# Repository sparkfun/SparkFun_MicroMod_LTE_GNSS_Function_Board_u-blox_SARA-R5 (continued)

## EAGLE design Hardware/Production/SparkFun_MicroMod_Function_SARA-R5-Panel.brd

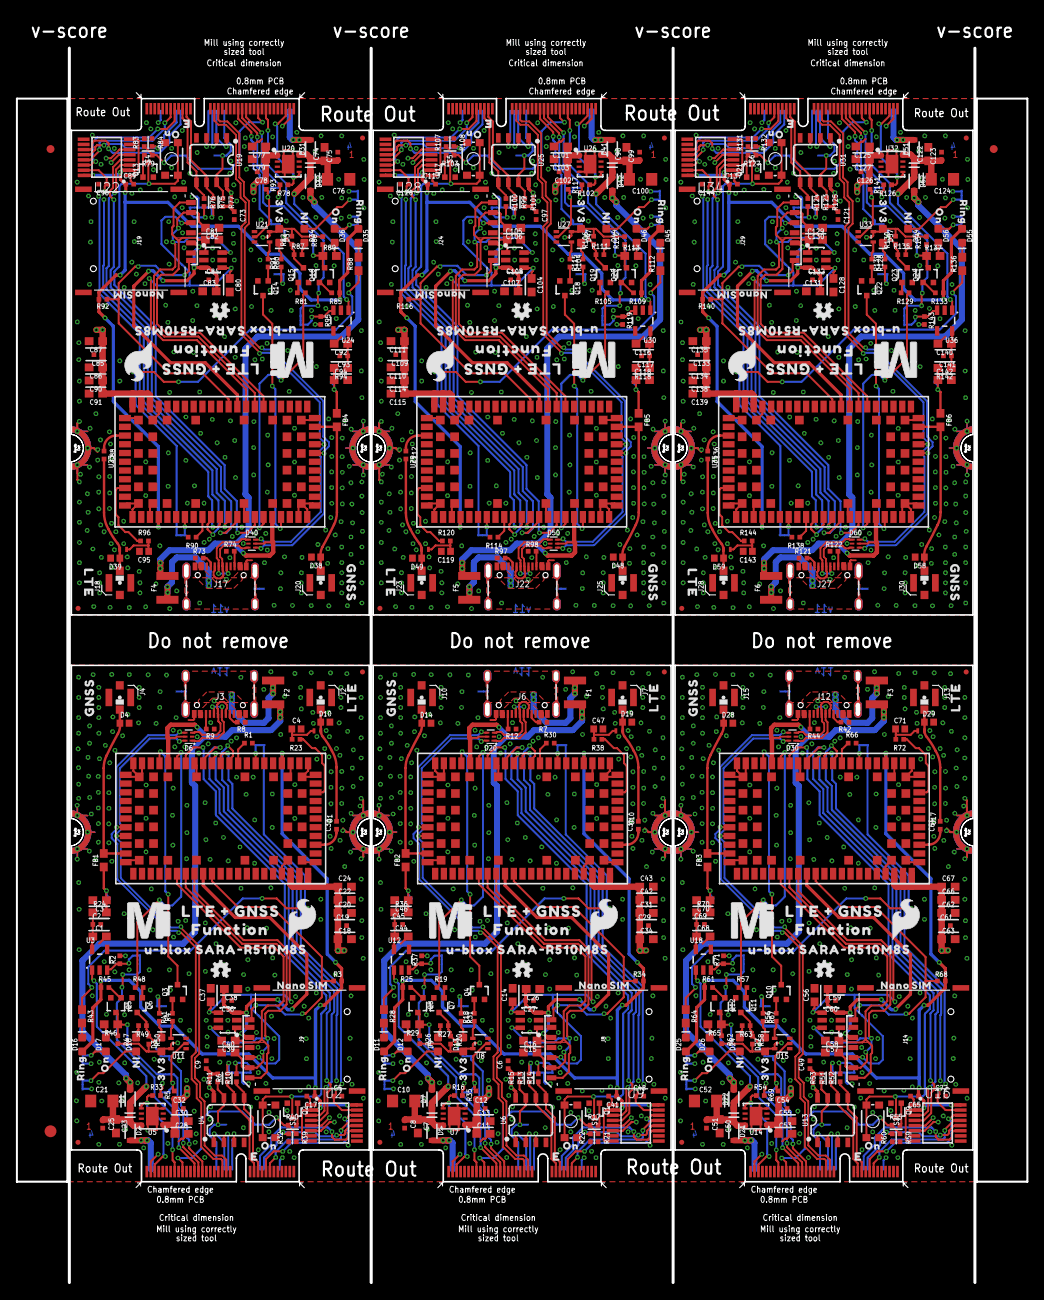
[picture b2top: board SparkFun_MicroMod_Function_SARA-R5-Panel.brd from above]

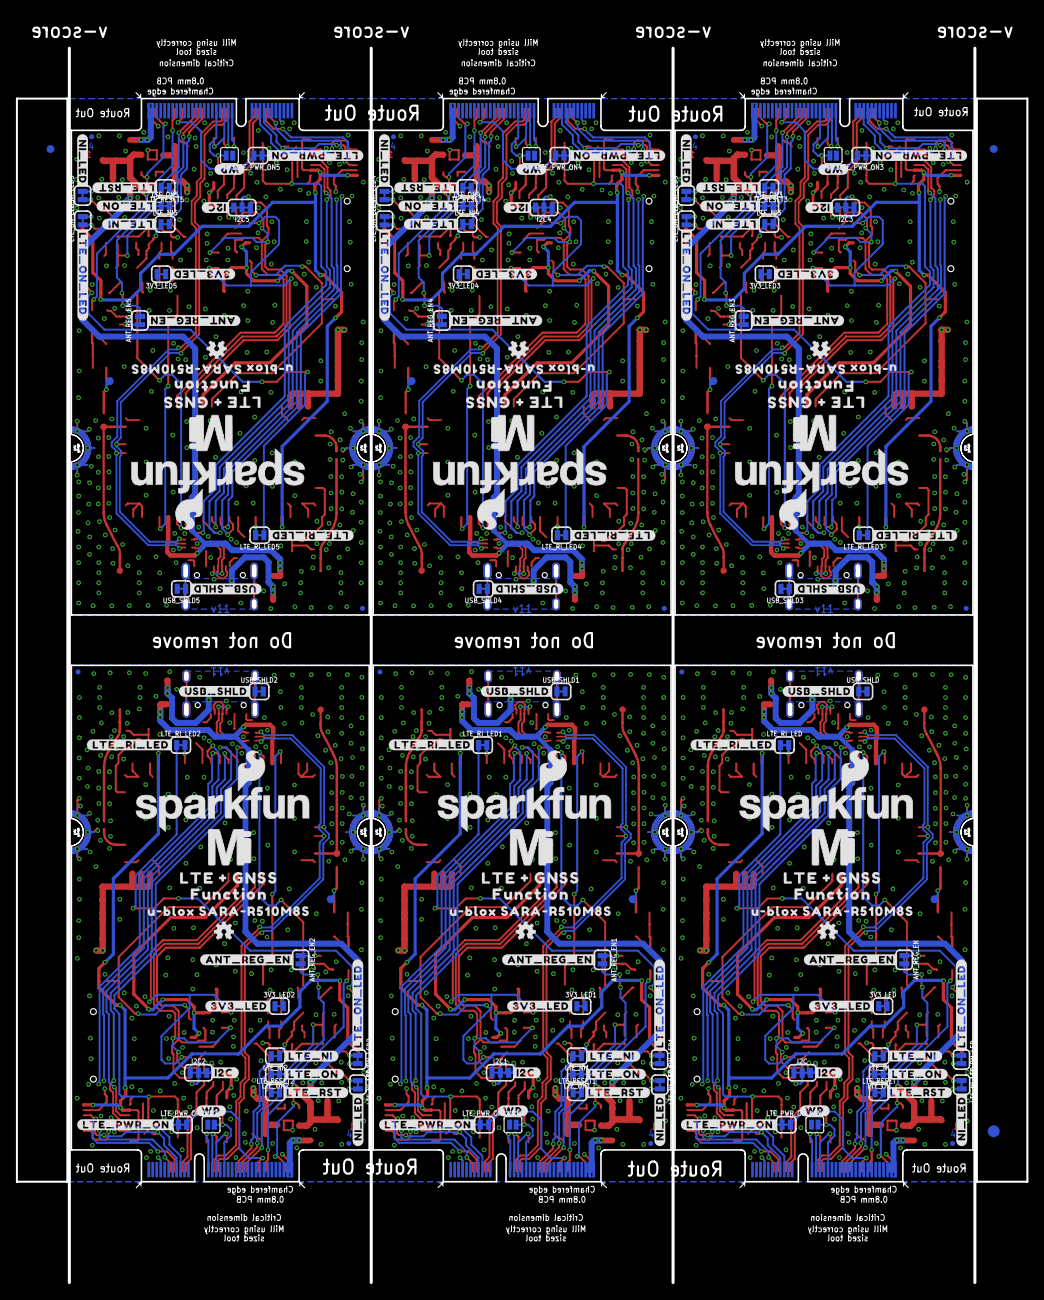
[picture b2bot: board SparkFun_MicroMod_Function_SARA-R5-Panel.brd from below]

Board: 4 copper layers, 127.2 x 155.4 mm, 768 parts (201 on the bottom side), 432 nets.

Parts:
3V3_LED, 3V3_LED1, 3V3_LED2, 3V3_LED3, 3V3_LED4, 3V3_LED5: JUMPER-SMT_2_NC_TRACE_SILK; SMT-JUMPER_2_NC_TRACE_SILK
ANT_REG_EN, ANT_REG_EN1, ANT_REG_EN2, ANT_REG_EN3, ANT_REG_EN4, ANT_REG_EN5: JUMPER-SMT_2_NC_TRACE_SILK; SMT-JUMPER_2_NC_TRACE_SILK
C1, C44, C68, C92, C116, C140: 1.0uF; 0603
C2, C5, C6, C8, C9, C12, C17, C19, C25, C27, C29, C32, C36, C41, C45, C48, C49, C51, C54, C60, C61, C65, C69, C72, C73, C75, C78, C84, C85, C89, C93, C96, C97, C99, C102, C108, C109, C113, C117, C120, C121, C123, C126, C132, C133, C137, C141, C144: 0.1uF; 0402-TIGHT
C3, C14, C15, C16, C26, C37, C38, C39, C40, C46, C56, C57, C58, C59, C70, C80, C81, C82, C83, C94, C104, C105, C106, C107, C118, C128, C129, C130, C131, C142: 47pF; 0603
C4, C47, C71, C95, C119, C143: 27pF; 0402
C7, C13, C23, C30, C50, C55, C74, C79, C98, C103, C122, C127: 0.22uF; 0603
C10, C21, C52, C76, C100, C124: 10uF; EIA3216
C11, C28, C53, C77, C101, C125: 4.7uF; 0603
C18, C34, C63, C87, C111, C135: 10uF; 0603
C20, C31, C62, C86, C110, C134: 68pF; 0603
C22, C42, C66, C90, C114, C138: 15pF; 0603
C24, C43, C67, C91, C115, C139: 8.2pF; 0603
C33, C35, C64, C88, C112, C136: 33pF; 0402-TIGHT
D1, D2, D5, D7, D21, D22, D31, D32, D41, D42, D51, D52: 3A/10V/280mV; SOD-323
D3, D11, D12, D13, D16, D17, D25, D26, D27, D35, D36, D37, D45, D46, D47, D55, D56, D57: RED; LED-0603
D4, D10, D14, D19, D28, D29, D38, D39, D48, D49, D58, D59: PESD0402-0402; 0402
D6, D20, D30, D40, D50, D60: PRTR5V0U2F; SOT886
D8, D15, D23, D33, D43, D53: DT1042-04SO-7; SOT23-6L
D9, D18, D24, D34, D44, D54: BLUE; LED-0603
E$1, E$2, E$3, E$4: FIDUCIAL-1X2
E$5, E$6: FIDUCIAL-1.5X3
F1, F2, F3, F4, F5, F6: 6V/2A; 1210
FB1, FB2, FB3, FB4, FB5, FB6: 30Ω/1.8A; 0603
FD1, FD2, FD3, FD4, FD5, FD6, FD7, FD8, FD9, FD10, FD11, FD12, FD13, FD14, FD15, FD16, FD17, FD18, FD19, FD20, FD21, FD22, FD23, FD24: FIDUCIALUFIDUCIAL; FIDUCIAL-MICRO
I2C, I2C1, I2C2, I2C3, I2C4, I2C5: JUMPER-SMT_3_2-NC_TRACE_SILK; SMT-JUMPER_3_2-NC_TRACE_SILK
J1, J5, J11, J16, J21, J26: MICROMOD_FUNCTION_STANDARD; M.2-CARD-E-22_FUNCTION_STANDARD
J2, J4, J7, J10, J13, J15, J18, J20, J23, J25, J28, J30: U.FL
J3, J6, J12, J17, J22, J27: USB-C-16P-2LAYER-PADS
J8, J9, J14, J19, J24, J29: NANO_SIM; NANO_SIM_PP
L1, L2, L3, L4, L5, L6: 68nH; 0402_COILCRAFT
LOGO1, LOGO3, LOGO9, LOGO13, LOGO17, LOGO21: SFE_LOGO_NAME_FLAME.2_INCH; SFE_LOGO_NAME_FLAME_.2
LOGO2, LOGO5, LOGO10, LOGO14, LOGO18, LOGO22: SFE_LOGO_FLAME.2_INCH; SFE_LOGO_FLAME_.2
LOGO4, LOGO6, LOGO7, LOGO8, LOGO11, LOGO12, LOGO15, LOGO16, LOGO19, LOGO20, LOGO23, LOGO24: OSHW-LOGOMINI; OSHW-LOGO-MINI
LTE_NI, LTE_NI1, LTE_NI2, LTE_NI3, LTE_NI4, LTE_NI5: JUMPER-SMT_2_NC_TRACE_SILK; SMT-JUMPER_2_NC_TRACE_SILK
LTE_NI_LED, LTE_NI_LED1, LTE_NI_LED2, LTE_NI_LED3, LTE_NI_LED4, LTE_NI_LED5: JUMPER-SMT_2_NC_TRACE_SILK; SMT-JUMPER_2_NC_TRACE_SILK
LTE_ON, LTE_ON1, LTE_ON2, LTE_ON3, LTE_ON4, LTE_ON5: JUMPER-SMT_2_NC_TRACE_SILK; SMT-JUMPER_2_NC_TRACE_SILK
LTE_ON_LED, LTE_ON_LED1, LTE_ON_LED2, LTE_ON_LED3, LTE_ON_LED4, LTE_ON_LED5: JUMPER-SMT_2_NC_TRACE_SILK; SMT-JUMPER_2_NC_TRACE_SILK
LTE_PWR_ON, LTE_PWR_ON1, LTE_PWR_ON2, LTE_PWR_ON3, LTE_PWR_ON4, LTE_PWR_ON5: JUMPER-SMT_2_NC_TRACE_SILK; SMT-JUMPER_2_NC_TRACE_SILK
LTE_RESET, LTE_RESET1, LTE_RESET2, LTE_RESET3, LTE_RESET4, LTE_RESET5: JUMPER-SMT_2_NC_TRACE_SILK; SMT-JUMPER_2_NC_TRACE_SILK
LTE_RI_LED, LTE_RI_LED1, LTE_RI_LED2, LTE_RI_LED3, LTE_RI_LED4, LTE_RI_LED5: JUMPER-SMT_2_NC_TRACE_SILK; SMT-JUMPER_2_NC_TRACE_SILK
Q1, Q2, Q3, Q4, Q5, Q6, Q7, Q8, Q9, Q10, Q11, Q12, Q13, Q14, Q15, Q16, Q17, Q18, Q19, Q20, Q21, Q22, Q23, Q24: 310mA/60V/1.6Ω; SOT323
R1, R2, R3, R20, R21, R22, R26, R30, R32, R34, R37, R39, R47, R50, R58, R59, R60, R62, R66, R68, R71, R82, R83, R84, R86, R90, R92, R95, R106, R107, R108, R110, R114, R116, R119, R130, R131, R132, R134, R138, R140, R143: 100k; 0402-TIGHT
R4, R31, R67, R91, R115, R139: 4.7k; 0402-TIGHT
R5, R11, R15, R23, R35, R38, R53, R69, R72, R77, R93, R96, R101, R117, R120, R125, R141, R144: 10k; 0402-TIGHT
R6, R10, R13, R14, R27, R49, R51, R52, R63, R75, R76, R87, R99, R100, R111, R123, R124, R135: 2.2k; 0402-TIGHT
R7, R8, R9, R12, R42, R44, R73, R74, R97, R98, R121, R122: 5.1k; 0402-TIGHT
R16, R33, R54, R78, R102, R126: DNP; 0402-TIGHT
R17, R18, R19, R25, R40, R41, R45, R48, R55, R56, R57, R61, R79, R80, R81, R85, R103, R104, R105, R109, R127, R128, R129, R133: 1k; 0402-TIGHT
R24, R36, R70, R94, R118, R142: 10; 0603
R28, R43, R64, R88, R112, R136: 240; 0603
R29, R46, R65, R89, R113, R137: 100; 0603
S1, S2, S3, S4, S5, S6: PWR_ON; TACTILE_SWITCH_SMD_4.6X2.8MM
TP1, TP2, TP3, TP4, TP5, TP22: TEST-POINT3X4; PAD.03X.04
U1, U10, U17, U23, U29, U35: SARA-R510M8S; SARA-LGA
U2, U9, U16, U22, U28, U34: SN74AVC4T774PW; SOP65P640X120-16N
U3, U12, U18, U24, U30, U36: 3.3V; SOT23-5
U4, U6, U13, U19, U25, U31: EEPROM; SO08
U5, U7, U14, U20, U26, U32: AP7361C-33FGE; UDFN-8
U8, U11, U15, U21, U27, U33: 74HC1G04; SOT353
U$1, U$50, U$81, U$110, U$140, U$169: #I2C#0
U$2, U$48, U$78, U$108, U$138, U$167: #ANT_REG_EN#0
U$3, U$12, U$35, U$36, U$65, U$66, U$95, U$96, U$124, U$125, U$154, U$155: MICROMOD_MI_LOGO_1
U$4, U$49, U$79, U$109, U$139, U$168: #3V3_LED#0
U$5, U$27, U$31, U$34, U$59, U$64, U$89, U$94, U$118, U$123, U$148, U$153: ON0
U$6, U$38, U$68, U$98, U$128, U$157: #LTE_ON#2
U$7, U$39, U$69, U$99, U$129, U$158: #LTE_NI#2
U$8, U$37, U$67, U$97, U$127, U$156: #LTE_PWR_ON#1
U$9, U$54, U$85, U$114, U$144, U$173: #NI_LED#0
U$10, U$25, U$56, U$87, U$116, U$146: #WP#0
U$11, U$14, U$40, U$45, U$70, U$75, U$100, U$105, U$130, U$135, U$159, U$164: LTE_#_GNSS0
U$13, U$19, U$41, U$46, U$71, U$76, U$101, U$106, U$131, U$136, U$160, U$165: FUNCTION0
U$15, U$20, U$42, U$47, U$72, U$77, U$102, U$107, U$132, U$137, U$161, U$166: U#BLOX_SARA#R510M8S0
U$16, U$43, U$73, U$103, U$133, U$162: LTE0
U$17, U$44, U$74, U$104, U$134, U$163: GNSS0
U$18, U$32, U$62, U$92, U$121, U$151: NANO0
U$21, U$51, U$82, U$111, U$141, U$170: #USB_SHLD#0
U$22, U$52, U$83, U$112, U$142, U$171: #LTE_RI_LED#0
U$23, U$53, U$84, U$113, U$143, U$172: #LTE_RST#0
U$24, U$55, U$86, U$115, U$145, U$174: #LTE_ON_LED#0
U$26, U$29, U$58, U$88, U$117, U$147: NI0
U$28, U$57, U$60, U$90, U$119, U$149: 3V34
U$30, U$61, U$80, U$91, U$120, U$150: RING0
U$33, U$63, U$93, U$122, U$126, U$152: SIM0
USB_SHLD, USB_SHLD1, USB_SHLD2, USB_SHLD3, USB_SHLD4, USB_SHLD5: JUMPER-SMT_2_NC_TRACE_SILK; SMT-JUMPER_2_NC_TRACE_SILK
WP, WP1, WP2, WP3, WP4, WP5: SMT-JUMPER_2_NO_SILK

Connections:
3.3V: C5.1, C9.1, C18.1, C19.1, C20.1, C22.1, C24.1, C28.1, C30.1, C32.1, D3.A, I2C.2, LTE_NI_LED.2, LTE_ON_LED.2, R5.1, R11.2, R47.2, R50.2, U1.51, U1.52, U1.53, U2.15, U4.8, U5.1, U11.5
3.3V1: C6.1, C11.1, C12.1, C13.1, C29.1, C31.1, C34.1, C42.1, C43.1, C48.1, D13.A, I2C1.2, LTE_NI_LED1.2, LTE_ON_LED1.2, R15.2, R20.2, R26.2, R35.1, U6.8, U7.1, U8.5, U9.15, U10.51, U10.52, U10.53
3.3V2: C49.1, C53.1, C54.1, C55.1, C61.1, C62.1, C63.1, C66.1, C67.1, C72.1, D27.A, I2C2.2, LTE_NI_LED2.2, LTE_ON_LED2.2, R53.2, R58.2, R62.2, R69.1, U13.8, U14.1, U15.5, U16.15, U17.51, U17.52, U17.53
3.3V3: C73.1, C77.1, C78.1, C79.1, C85.1, C86.1, C87.1, C90.1, C91.1, C96.1, D37.A, I2C3.2, LTE_NI_LED3.2, LTE_ON_LED3.2, R77.2, R82.2, R86.2, R93.1, U19.8, U20.1, U21.5, U22.15, U23.51, U23.52, U23.53
3.3V4: C97.1, C101.1, C102.1, C103.1, C109.1, C110.1, C111.1, C114.1, C115.1, C120.1, D47.A, I2C4.2, LTE_NI_LED4.2, LTE_ON_LED4.2, R101.2, R106.2, R110.2, R117.1, U25.8, U26.1, U27.5, U28.15, U29.51, U29.52, U29.53
3.3V5: C121.1, C125.1, C126.1, C127.1, C133.1, C134.1, C135.1, C138.1, C139.1, C144.1, D57.A, I2C5.2, LTE_NI_LED5.2, LTE_ON_LED5.2, R125.2, R130.2, R134.2, R141.1, U31.8, U32.1, U33.5, U34.15, U35.51, U35.52, U35.53
3.3V_IN: J1.73, R2.2, R33.2
3.3V_IN1: J5.73, R16.2, R37.2
3.3V_IN2: J11.73, R54.2, R71.2
3.3V_IN3: J16.73, R78.2, R95.2
3.3V_IN4: J21.73, R102.2, R119.2
3.3V_IN5: J26.73, R126.2, R143.2
ANT_REG_EN: ANT_REG_EN.1, R2.1, U3.3
ANT_REG_EN1: ANT_REG_EN1.1, R37.1, U12.3
ANT_REG_EN2: ANT_REG_EN2.1, R71.1, U18.3
ANT_REG_EN3: ANT_REG_EN3.1, R95.1, U24.3
ANT_REG_EN4: ANT_REG_EN4.1, R119.1, U30.3
ANT_REG_EN5: ANT_REG_EN5.1, R143.1, U36.3
CTS: J1.18, U2.11
CTS1: J5.18, U9.11
CTS2: J11.18, U16.11
CTS3: J16.18, U22.11
CTS4: J21.18, U28.11
CTS5: J26.18, U34.11
EN: J1.71, R33.1, U5.5
EN1: J5.71, R16.1, U7.5
EN2: J11.71, R54.1, U14.5
EN3: J16.71, R78.1, U20.5
EN4: J21.71, R102.1, U26.5
EN5: J26.71, R126.1, U32.5
EWP: J1.40, R11.1, U4.7, WP.2
EWP1: J5.40, R15.1, U6.7, WP1.2
EWP2: J11.40, R53.1, U13.7, WP2.2
EWP3: J16.40, R77.1, U19.7, WP3.2
EWP4: J21.40, R101.1, U25.7, WP4.2
EWP5: J26.40, R125.1, U31.7, WP5.2
GND: 3V3_LED.1, C1.2, C2.2, C3.2, C4.2, C5.2, C9.2, C17.2, C18.2, C19.2, C20.2, C21.-, C22.2, C23.2, C24.2, C25.2, C28.2, C30.2, C32.2, C36.1, C37.2, C38.1, C39.2, C40.1, D4.2, D6.2, D10.2, D15.2, D15.5, J1.1, J1.2, J1.8, J1.33, J1.39, J1.45, J1.75, J1.GND1, J1.GND2, J1.GND3, J1.GND4, J1.GND5, J1.GND6, J2.1, J2.2, J3.GND, J3.GND2, J4.1, J4.2, J9.A1, J9.A2, J9.A3, J9.A4, J9.C5, Q2.2, Q3.2, Q5.2, Q6.2, R1.2, R8.1, R9.1, R32.1, R39.2, S3.3, S3.4, U1.1, U1.3, U1.5, U1.14, U1.20, U1.21, U1.22, U1.30, U1.32, U1.43, U1.50, U1.54, U1.55, U1.57, U1.58, U1.59, U1.60, U1.61, U1.63, U1.64, U1.65, U1.66, U1.67, U1.68, U1.69, U1.70, U1.71, U1.72, U1.73, U1.74, U1.75, U1.76, U1.77, U1.78, U1.79, U1.80, U1.81, U1.82, U1.83, U1.84, U1.85, U1.86, U1.87, U1.88, U1.89, U1.90, U1.91, U1.92, U1.93, U1.94, U1.95, U1.96, U2.1, U2.7, U2.9, U2.10, U3.2, U4.4, U5.4, U5.EP, U11.3, USB_SHLD.2, WP.1
GND1: 3V3_LED1.1, C6.2, C7.2, C8.2, C10.-, C11.2, C12.2, C13.2, C14.2, C15.2, C16.1, C26.1, C27.1, C29.2, C31.2, C34.2, C41.2, C42.2, C43.2, C44.2, C45.2, C46.2, C47.2, C48.2, D8.2, D8.5, D14.2, D19.2, D20.2, J5.1, J5.2, J5.8, J5.33, J5.39, J5.45, J5.75, J5.GND1, J5.GND2, J5.GND3, J5.GND4, J5.GND5, J5.GND6, J6.GND, J6.GND2, J7.1, J7.2, J8.A1, J8.A2, J8.A3, J8.A4, J8.C5, J10.1, J10.2, Q1.2, Q4.2, Q7.2, Q8.2, R7.1, R12.1, R21.2, R22.1, R30.2, S1.3, S1.4, U6.4, U7.4, U7.EP, U8.3, U9.1, U9.7, U9.9, U9.10, U10.1, U10.3, U10.5, U10.14, U10.20, U10.21, U10.22, U10.30, U10.32, U10.43, U10.50, U10.54, U10.55, U10.57, U10.58, U10.59, U10.60, U10.61, U10.63, U10.64, U10.65, U10.66, U10.67, U10.68, U10.69, U10.70, U10.71, U10.72, U10.73, U10.74, U10.75, U10.76, U10.77, U10.78, U10.79, U10.80, U10.81, U10.82, U10.83, U10.84, U10.85, U10.86, U10.87, U10.88, U10.89, U10.90, U10.91, U10.92, U10.93, U10.94, U10.95, U10.96, U12.2, USB_SHLD1.2, WP1.1
GND2: 3V3_LED2.1, C49.2, C50.2, C51.2, C52.-, C53.2, C54.2, C55.2, C56.2, C57.2, C58.1, C59.1, C60.1, C61.2, C62.2, C63.2, C65.2, C66.2, C67.2, C68.2, C69.2, C70.2, C71.2, C72.2, D23.2, D23.5, D28.2, D29.2, D30.2, J11.1, J11.2, J11.8, J11.33, J11.39, J11.45, J11.75, J11.GND1, J11.GND2, J11.GND3, J11.GND4, J11.GND5, J11.GND6, J12.GND, J12.GND2, J13.1, J13.2, J14.A1, J14.A2, J14.A3, J14.A4, J14.C5, J15.1, J15.2, Q9.2, Q10.2, Q11.2, Q12.2, R42.1, R44.1, R59.2, R60.1, R66.2, S2.3, S2.4, U13.4, U14.4, U14.EP, U15.3, U16.1, U16.7, U16.9, U16.10, U17.1, U17.3, U17.5, U17.14, U17.20, U17.21, U17.22, U17.30, U17.32, U17.43, U17.50, U17.54, U17.55, U17.57, U17.58, U17.59, U17.60, U17.61, U17.63, U17.64, U17.65, U17.66, U17.67, U17.68, U17.69, U17.70, U17.71, U17.72, U17.73, U17.74, U17.75, U17.76, U17.77, U17.78, U17.79, U17.80, U17.81, U17.82, U17.83, U17.84, U17.85, U17.86, U17.87, U17.88, U17.89, U17.90, U17.91, U17.92, U17.93, U17.94, U17.95, U17.96, U18.2, USB_SHLD2.2, WP2.1
GND3: 3V3_LED3.1, C73.2, C74.2, C75.2, C76.-, C77.2, C78.2, C79.2, C80.2, C81.2, C82.1, C83.1, C84.1, C85.2, C86.2, C87.2, C89.2, C90.2, C91.2, C92.2, C93.2, C94.2, C95.2, C96.2, D33.2, D33.5, D38.2, D39.2, D40.2, J16.1, J16.2, J16.8, J16.33, J16.39, J16.45, J16.75, J16.GND1, J16.GND2, J16.GND3, J16.GND4, J16.GND5, J16.GND6, J17.GND, J17.GND2, J18.1, J18.2, J19.A1, J19.A2, J19.A3, J19.A4, J19.C5, J20.1, J20.2, Q13.2, Q14.2, Q15.2, Q16.2, R73.1, R74.1, R83.2, R84.1, R90.2, S4.3, S4.4, U19.4, U20.4, U20.EP, U21.3, U22.1, U22.7, U22.9, U22.10, U23.1, U23.3, U23.5, U23.14, U23.20, U23.21, U23.22, U23.30, U23.32, U23.43, U23.50, U23.54, U23.55, U23.57, U23.58, U23.59, U23.60, U23.61, U23.63, U23.64, U23.65, U23.66, U23.67, U23.68, U23.69, U23.70, U23.71, U23.72, U23.73, U23.74, U23.75, U23.76, U23.77, U23.78, U23.79, U23.80, U23.81, U23.82, U23.83, U23.84, U23.85, U23.86, U23.87, U23.88, U23.89, U23.90, U23.91, U23.92, U23.93, U23.94, U23.95, U23.96, U24.2, USB_SHLD3.2, WP3.1
GND4: 3V3_LED4.1, C97.2, C98.2, C99.2, C100.-, C101.2, C102.2, C103.2, C104.2, C105.2, C106.1, C107.1, C108.1, C109.2, C110.2, C111.2, C113.2, C114.2, C115.2, C116.2, C117.2, C118.2, C119.2, C120.2, D43.2, D43.5, D48.2, D49.2, D50.2, J21.1, J21.2, J21.8, J21.33, J21.39, J21.45, J21.75, J21.GND1, J21.GND2, J21.GND3, J21.GND4, J21.GND5, J21.GND6, J22.GND, J22.GND2, J23.1, J23.2, J24.A1, J24.A2, J24.A3, J24.A4, J24.C5, J25.1, J25.2, Q17.2, Q18.2, Q19.2, Q20.2, R97.1, R98.1, R107.2, R108.1, R114.2, S5.3, S5.4, U25.4, U26.4, U26.EP, U27.3, U28.1, U28.7, U28.9, U28.10, U29.1, U29.3, U29.5, U29.14, U29.20, U29.21, U29.22, U29.30, U29.32, U29.43, U29.50, U29.54, U29.55, U29.57, U29.58, U29.59, U29.60, U29.61, U29.63, U29.64, U29.65, U29.66, U29.67, U29.68, U29.69, U29.70, U29.71, U29.72, U29.73, U29.74, U29.75, U29.76, U29.77, U29.78, U29.79, U29.80, U29.81, U29.82, U29.83, U29.84, U29.85, U29.86, U29.87, U29.88, U29.89, U29.90, U29.91, U29.92, U29.93, U29.94, U29.95, U29.96, U30.2, USB_SHLD4.2, WP4.1
GND5: 3V3_LED5.1, C121.2, C122.2, C123.2, C124.-, C125.2, C126.2, C127.2, C128.2, C129.2, C130.1, C131.1, C132.1, C133.2, C134.2, C135.2, C137.2, C138.2, C139.2, C140.2, C141.2, C142.2, C143.2, C144.2, D53.2, D53.5, D58.2, D59.2, D60.2, J26.1, J26.2, J26.8, J26.33, J26.39, J26.45, J26.75, J26.GND1, J26.GND2, J26.GND3, J26.GND4, J26.GND5, J26.GND6, J27.GND, J27.GND2, J28.1, J28.2, J29.A1, J29.A2, J29.A3, J29.A4, J29.C5, J30.1, J30.2, Q21.2, Q22.2, Q23.2, Q24.2, R121.1, R122.1, R131.2, R132.1, R138.2, S6.3, S6.4, U31.4, U32.4, U32.EP, U33.3, U34.1, U34.7, U34.9, U34.10, U35.1, U35.3, U35.5, U35.14, U35.20, U35.21, U35.22, U35.30, U35.32, U35.43, U35.50, U35.54, U35.55, U35.57, U35.58, U35.59, U35.60, U35.61, U35.63, U35.64, U35.65, U35.66, U35.67, U35.68, U35.69, U35.70, U35.71, U35.72, U35.73, U35.74, U35.75, U35.76, U35.77, U35.78, U35.79, U35.80, U35.81, U35.82, U35.83, U35.84, U35.85, U35.86, U35.87, U35.88, U35.89, U35.90, U35.91, U35.92, U35.93, U35.94, U35.95, U35.96, U36.2, USB_SHLD5.2, WP5.1
GNSS_ANT: D4.1, FB1.2, J4.FEED, U1.31
GNSS_ANT1: D14.1, FB2.2, J10.FEED, U10.31
GNSS_ANT2: D28.1, FB3.2, J15.FEED, U17.31
GNSS_ANT3: D38.1, FB4.2, J20.FEED, U23.31
GNSS_ANT4: D48.1, FB5.2, J25.FEED, U29.31
GNSS_ANT5: D58.1, FB6.2, J30.FEED, U35.31
I2C_SCL: J1.21, R6.1, U4.6
I2C_SCL1: J5.21, R13.1, U6.6
I2C_SCL2: J11.21, R51.1, U13.6
I2C_SCL3: J16.21, R75.1, U19.6
I2C_SCL4: J21.21, R99.1, U25.6
I2C_SCL5: J26.21, R123.1, U31.6
I2C_SDA: J1.19, R10.1, U4.5
I2C_SDA1: J5.19, R14.1, U6.5
I2C_SDA2: J11.19, R52.1, U13.5
I2C_SDA3: J16.19, R76.1, U19.5
I2C_SDA4: J21.19, R100.1, U25.5
I2C_SDA5: J26.19, R124.1, U31.5
LTE_18_!RESET!: Q3.3, U1.18
LTE_18_!RESET!1: Q4.3, U10.18
LTE_18_!RESET!2: Q10.3, U17.18
LTE_18_!RESET!3: Q14.3, U23.18
LTE_18_!RESET!4: Q18.3, U29.18
LTE_18_!RESET!5: Q22.3, U35.18
LTE_18_CTS: U1.11, U2.6
LTE_18_CTS1: U9.6, U10.11
LTE_18_CTS2: U16.6, U17.11
LTE_18_CTS3: U22.6, U23.11
LTE_18_CTS4: U28.6, U29.11
LTE_18_CTS5: U34.6, U35.11
LTE_18_DTR: R1.1, U1.9
LTE_18_DTR1: R30.1, U10.9
LTE_18_DTR2: R66.1, U17.9
LTE_18_DTR3: R90.1, U23.9
LTE_18_DTR4: R114.1, U29.9
LTE_18_DTR5: R138.1, U35.9
LTE_18_NI: R48.1, U1.16
LTE_18_NI1: R19.1, U10.16
LTE_18_NI2: R57.1, U17.16
LTE_18_NI3: R81.1, U23.16
LTE_18_NI4: R105.1, U29.16
LTE_18_NI5: R129.1, U35.16
LTE_18_PWR_ON: Q2.3, S3.1, S3.2, U1.15
LTE_18_PWR_ON1: Q1.3, S1.1, S1.2, U10.15
LTE_18_PWR_ON2: Q9.3, S2.1, S2.2, U17.15
LTE_18_PWR_ON3: Q13.3, S4.1, S4.2, U23.15
LTE_18_PWR_ON4: Q17.3, S5.1, S5.2, U29.15
LTE_18_PWR_ON5: Q21.3, S6.1, S6.2, U35.15
LTE_18_RI: LTE_RI_LED.2, U1.7
LTE_18_RI1: LTE_RI_LED1.2, U10.7
LTE_18_RI2: LTE_RI_LED2.2, U17.7
LTE_18_RI3: LTE_RI_LED3.2, U23.7
LTE_18_RI4: LTE_RI_LED4.2, U29.7
LTE_18_RI5: LTE_RI_LED5.2, U35.7
LTE_18_RTS: U1.10, U2.5
LTE_18_RTS1: U9.5, U10.10
LTE_18_RTS2: U16.5, U17.10
LTE_18_RTS3: U22.5, U23.10
LTE_18_RTS4: U28.5, U29.10
LTE_18_RTS5: U34.5, U35.10
LTE_18_RXO: U1.13, U2.4
LTE_18_RXO1: U9.4, U10.13
LTE_18_RXO2: U16.4, U17.13
LTE_18_RXO3: U22.4, U23.13
LTE_18_RXO4: U28.4, U29.13
LTE_18_RXO5: U34.4, U35.13
LTE_18_TXI: U1.12, U2.3
LTE_18_TXI1: U9.3, U10.12
LTE_18_TXI2: U16.3, U17.12
LTE_18_TXI3: U22.3, U23.12
LTE_18_TXI4: U28.3, U29.12
LTE_18_TXI5: U34.3, U35.12
LTE_!NI!: LTE_NI.1, Q6.3, R49.1, R50.1
LTE_!NI!1: LTE_NI1.1, Q7.3, R20.1, R27.1
LTE_!NI!2: LTE_NI2.1, Q11.3, R58.1, R63.1
LTE_!NI!3: LTE_NI3.1, Q15.3, R82.1, R87.1
LTE_!NI!4: LTE_NI4.1, Q19.3, R106.1, R111.1
LTE_!NI!5: LTE_NI5.1, Q23.3, R130.1, R135.1
LTE_!ON!: LTE_ON.1, Q5.3, R46.1, R47.1
LTE_!ON!1: LTE_ON1.1, Q8.3, R26.1, R29.1
LTE_!ON!2: LTE_ON2.1, Q12.3, R62.1, R65.1
LTE_!ON!3: LTE_ON3.1, Q16.3, R86.1, R89.1
LTE_!ON!4: LTE_ON4.1, Q20.3, R110.1, R113.1
LTE_!ON!5: LTE_ON5.1, Q24.3, R134.1, R137.1
LTE_!RESET!: LTE_RESET.1, R5.2, U11.2
LTE_!RESET!1: LTE_RESET1.1, R35.2, U8.2
LTE_!RESET!2: LTE_RESET2.1, R69.2, U15.2
LTE_!RESET!3: LTE_RESET3.1, R93.2, U21.2
LTE_!RESET!4: LTE_RESET4.1, R117.2, U27.2
LTE_!RESET!5: LTE_RESET5.1, R141.2, U33.2
LTE_ANT: C33.1, U1.56
LTE_ANT1: C35.1, U10.56
LTE_ANT2: C64.1, U17.56
LTE_ANT3: C88.1, U23.56
LTE_ANT4: C112.1, U29.56
LTE_ANT5: C136.1, U35.56
LTE_PWR_ON: LTE_PWR_ON.1, R39.1, R40.1
LTE_PWR_ON1: LTE_PWR_ON1.1, R17.1, R21.1
LTE_PWR_ON2: LTE_PWR_ON2.1, R55.1, R59.1
LTE_PWR_ON3: LTE_PWR_ON3.1, R79.1, R83.1
LTE_PWR_ON4: LTE_PWR_ON4.1, R103.1, R107.1
LTE_PWR_ON5: LTE_PWR_ON5.1, R127.1, R131.1
unnamed: J1.36, U4.1
unnamed: J3.A5, R8.2
unnamed: J1.57, LTE_PWR_ON.2
unnamed: ANT_REG_EN.2, J1.61
unnamed: J3.B5, R9.2
unnamed: 3V3_LED.2, R4.1
unnamed: D3.C, R4.2
unnamed: J1.32, U4.3
unnamed: J1.34, U4.2
unnamed: D6.1, J3.A6, J3.B6
unnamed: C33.2, D10.1, J2.FEED, L2.P$2
unnamed: J1.47, LTE_NI.2
unnamed: I2C.1, R10.2
unnamed: I2C.3, R6.2
unnamed: D6.3, J3.A7, J3.B7
unnamed: J1.49, LTE_ON.2
unnamed: J1.51, LTE_RESET.2
unnamed: C4.1, L2.P$1, R23.2
unnamed: D18.A, LTE_NI_LED.1
unnamed: LTE_RI_LED.1, R43.1
unnamed: D17.A, LTE_ON_LED.1
unnamed: F2.1, J3.VBUS1, J3.VBUS2
unnamed: 3V3_LED1.2, R31.1
unnamed: C1.1, C2.1, R24.1, U3.5
unnamed: C3.1, FB1.1, R24.2, TP22.1
unnamed: Q2.1, R40.2
unnamed: Q3.1, R41.2
unnamed: R41.1, U11.4
unnamed: D13.C, R31.2
unnamed: J6.A5, R7.2
unnamed: J6.B5, R12.2
unnamed: J5.32, U6.3
unnamed: J5.34, U6.2
unnamed: D16.C, R43.2
unnamed: Q6.1, R48.2
unnamed: J5.36, U6.1
unnamed: D18.C, R49.2
unnamed: I2C1.1, R14.2
unnamed: I2C1.3, R13.2
unnamed: LTE_RI_LED1.1, R28.1
unnamed: D11.C, R28.2
unnamed: Q7.1, R19.2
unnamed: D9.C, R27.2
unnamed: Q8.1, R25.2
unnamed: D12.C, R29.2
unnamed: Q1.1, R17.2
unnamed: Q5.1, R45.2
unnamed: Q4.1, R18.2
unnamed: D17.C, R46.2
unnamed: R18.1, U8.4
unnamed: J5.57, LTE_PWR_ON1.2
unnamed: J5.51, LTE_RESET1.2
unnamed: J5.47, LTE_NI1.2
unnamed: J5.49, LTE_ON1.2
unnamed: C44.1, C45.1, R36.1, U12.5
unnamed: C46.1, FB2.1, R36.2, TP1.1
unnamed: ANT_REG_EN1.2, J5.61
unnamed: C35.2, D19.1, J7.FEED, L1.P$2
unnamed: C47.1, L1.P$1, R38.2
unnamed: D20.3, J6.A7, J6.B7
unnamed: D20.1, J6.A6, J6.B6
unnamed: D9.A, LTE_NI_LED1.1
unnamed: D12.A, LTE_ON_LED1.1
unnamed: F1.1, J6.VBUS1, J6.VBUS2
unnamed: 3V3_LED2.2, R67.1
unnamed: D27.C, R67.2
unnamed: J12.A5, R42.2
unnamed: J12.B5, R44.2
unnamed: J11.32, U13.3
unnamed: J11.34, U13.2
unnamed: J11.36, U13.1
unnamed: I2C2.1, R52.2
unnamed: I2C2.3, R51.2
unnamed: LTE_RI_LED2.1, R64.1
unnamed: D25.C, R64.2
unnamed: Q11.1, R57.2
unnamed: D24.C, R63.2
unnamed: Q12.1, R61.2
unnamed: D26.C, R65.2
unnamed: Q9.1, R55.2
unnamed: Q10.1, R56.2
unnamed: R56.1, U15.4
unnamed: J11.57, LTE_PWR_ON2.2
unnamed: J11.51, LTE_RESET2.2
unnamed: J11.47, LTE_NI2.2
unnamed: J11.49, LTE_ON2.2
unnamed: C68.1, C69.1, R70.1, U18.5
unnamed: C70.1, FB3.1, R70.2, TP2.1
unnamed: ANT_REG_EN2.2, J11.61
unnamed: C64.2, D29.1, J13.FEED, L3.P$2
unnamed: C71.1, L3.P$1, R72.2
unnamed: D30.3, J12.A7, J12.B7
unnamed: D30.1, J12.A6, J12.B6
unnamed: D24.A, LTE_NI_LED2.1
unnamed: D26.A, LTE_ON_LED2.1
unnamed: F3.1, J12.VBUS1, J12.VBUS2
unnamed: 3V3_LED3.2, R91.1
unnamed: D37.C, R91.2
unnamed: J17.A5, R73.2
unnamed: J17.B5, R74.2
unnamed: J16.32, U19.3
unnamed: J16.34, U19.2
unnamed: J16.36, U19.1
unnamed: I2C3.1, R76.2
unnamed: I2C3.3, R75.2
unnamed: LTE_RI_LED3.1, R88.1
unnamed: D35.C, R88.2
unnamed: Q15.1, R81.2
unnamed: D34.C, R87.2
unnamed: Q16.1, R85.2
unnamed: D36.C, R89.2
unnamed: Q13.1, R79.2
unnamed: Q14.1, R80.2
unnamed: R80.1, U21.4
unnamed: J16.57, LTE_PWR_ON3.2
unnamed: J16.51, LTE_RESET3.2
unnamed: J16.47, LTE_NI3.2
unnamed: J16.49, LTE_ON3.2
unnamed: C92.1, C93.1, R94.1, U24.5
unnamed: C94.1, FB4.1, R94.2, TP3.1
unnamed: ANT_REG_EN3.2, J16.61
unnamed: C88.2, D39.1, J18.FEED, L4.P$2
unnamed: C95.1, L4.P$1, R96.2
unnamed: D40.3, J17.A7, J17.B7
unnamed: D40.1, J17.A6, J17.B6
unnamed: D34.A, LTE_NI_LED3.1
unnamed: D36.A, LTE_ON_LED3.1
unnamed: F4.1, J17.VBUS1, J17.VBUS2
unnamed: 3V3_LED4.2, R115.1
unnamed: D47.C, R115.2
unnamed: J22.A5, R97.2
unnamed: J22.B5, R98.2
unnamed: J21.32, U25.3
unnamed: J21.34, U25.2
unnamed: J21.36, U25.1
unnamed: I2C4.1, R100.2
unnamed: I2C4.3, R99.2
unnamed: LTE_RI_LED4.1, R112.1
unnamed: D45.C, R112.2
unnamed: Q19.1, R105.2
unnamed: D44.C, R111.2
unnamed: Q20.1, R109.2
unnamed: D46.C, R113.2
unnamed: Q17.1, R103.2
unnamed: Q18.1, R104.2
unnamed: R104.1, U27.4
unnamed: J21.57, LTE_PWR_ON4.2
unnamed: J21.51, LTE_RESET4.2
unnamed: J21.47, LTE_NI4.2
unnamed: J21.49, LTE_ON4.2
unnamed: C116.1, C117.1, R118.1, U30.5
unnamed: C118.1, FB5.1, R118.2, TP4.1
unnamed: ANT_REG_EN4.2, J21.61
unnamed: C112.2, D49.1, J23.FEED, L5.P$2
unnamed: C119.1, L5.P$1, R120.2
unnamed: D50.3, J22.A7, J22.B7
unnamed: D50.1, J22.A6, J22.B6
unnamed: D44.A, LTE_NI_LED4.1
unnamed: D46.A, LTE_ON_LED4.1
unnamed: F5.1, J22.VBUS1, J22.VBUS2
unnamed: 3V3_LED5.2, R139.1
unnamed: D57.C, R139.2
unnamed: J27.A5, R121.2
unnamed: J27.B5, R122.2
unnamed: J26.32, U31.3
unnamed: J26.34, U31.2
unnamed: J26.36, U31.1
unnamed: I2C5.1, R124.2
unnamed: I2C5.3, R123.2
unnamed: LTE_RI_LED5.1, R136.1
unnamed: D55.C, R136.2
unnamed: Q23.1, R129.2
unnamed: D54.C, R135.2
unnamed: Q24.1, R133.2
unnamed: D56.C, R137.2
unnamed: Q21.1, R127.2
unnamed: Q22.1, R128.2
unnamed: R128.1, U33.4
unnamed: J26.57, LTE_PWR_ON5.2
unnamed: J26.51, LTE_RESET5.2
unnamed: J26.47, LTE_NI5.2
unnamed: J26.49, LTE_ON5.2
unnamed: C140.1, C141.1, R142.1, U36.5
unnamed: C142.1, FB6.1, R142.2, TP5.1
unnamed: ANT_REG_EN5.2, J26.61
unnamed: C136.2, D59.1, J28.FEED, L6.P$2
unnamed: C143.1, L6.P$1, R144.2
unnamed: D60.3, J27.A7, J27.B7
unnamed: D60.1, J27.A6, J27.B6
unnamed: D54.A, LTE_NI_LED5.1
unnamed: D56.A, LTE_ON_LED5.1
unnamed: F6.1, J27.VBUS1, J27.VBUS2
RTS: J1.16, R32.2, U2.12
RTS1: J5.16, R22.2, U9.12
RTS2: J11.16, R60.2, U16.12
RTS3: J16.16, R84.2, U22.12
RTS4: J21.16, R108.2, U28.12
RTS5: J26.16, R132.2, U34.12
RX: J1.15, U2.14
RX1: J5.15, U9.14
RX2: J11.15, U16.14
RX3: J16.15, U22.14
RX4: J21.15, U28.14
RX5: J26.15, U34.14
SARA_ANT_DET: R23.1, U1.62
SARA_ANT_DET1: R38.1, U10.62
SARA_ANT_DET2: R72.1, U17.62
SARA_ANT_DET3: R96.1, U23.62
SARA_ANT_DET4: R120.1, U29.62
SARA_ANT_DET5: R144.1, U35.62
SHLD: J3.SHLD1, J3.SHLD2, J3.SHLD3, J3.SHLD4, USB_SHLD.1
SHLD1: J6.SHLD1, J6.SHLD2, J6.SHLD3, J6.SHLD4, USB_SHLD1.1
SHLD2: J12.SHLD1, J12.SHLD2, J12.SHLD3, J12.SHLD4, USB_SHLD2.1
SHLD3: J17.SHLD1, J17.SHLD2, J17.SHLD3, J17.SHLD4, USB_SHLD3.1
SHLD4: J22.SHLD1, J22.SHLD2, J22.SHLD3, J22.SHLD4, USB_SHLD4.1
SHLD5: J27.SHLD1, J27.SHLD2, J27.SHLD3, J27.SHLD4, USB_SHLD5.1
SIM_CLK: C39.1, D15.1, J9.C3, U1.38
SIM_CLK1: C15.1, D8.1, J8.C3, U10.38
SIM_CLK2: C57.1, D23.1, J14.C3, U17.38
SIM_CLK3: C81.1, D33.1, J19.C3, U23.38
SIM_CLK4: C105.1, D43.1, J24.C3, U29.38
SIM_CLK5: C129.1, D53.1, J29.C3, U35.38
SIM_DET: J9.CD, R3.1, U1.42
SIM_DET1: J8.CD, R34.1, U10.42
SIM_DET2: J14.CD, R68.1, U17.42
SIM_DET3: J19.CD, R92.1, U23.42
SIM_DET4: J24.CD, R116.1, U29.42
SIM_DET5: J29.CD, R140.1, U35.42
SIM_IO: C40.2, D15.6, J9.C7, U1.39
SIM_IO1: C16.2, D8.6, J8.C7, U10.39
SIM_IO2: C58.2, D23.6, J14.C7, U17.39
SIM_IO3: C82.2, D33.6, J19.C7, U23.39
SIM_IO4: C106.2, D43.6, J24.C7, U29.39
SIM_IO5: C130.2, D53.6, J29.C7, U35.39
SIM_RST: C37.1, D15.4, J9.C2, U1.40
SIM_RST1: C14.1, D8.4, J8.C2, U10.40
SIM_RST2: C56.1, D23.4, J14.C2, U17.40
SIM_RST3: C80.1, D33.4, J19.C2, U23.40
SIM_RST4: C104.1, D43.4, J24.C2, U29.40
SIM_RST5: C128.1, D53.4, J29.C2, U35.40
TX: J1.13, U2.13
TX1: J5.13, U9.13
TX2: J11.13, U16.13
TX3: J16.13, U22.13
TX4: J21.13, U28.13
TX5: J26.13, U34.13
USB_N: D6.4, J1.37, U1.28
USB_N1: D20.4, J5.37, U10.28
USB_N2: D30.4, J11.37, U17.28
USB_N3: D40.4, J16.37, U23.28
USB_N4: D50.4, J21.37, U29.28
USB_N5: D60.4, J26.37, U35.28
USB_P: D6.6, J1.35, U1.29
USB_P1: D20.6, J5.35, U10.29
USB_P2: D30.6, J11.35, U17.29
USB_P3: D40.6, J16.35, U23.29
USB_P4: D50.6, J21.35, U29.29
USB_P5: D60.6, J26.35, U35.29
VCC: D2.A, J1.72, J1.74
VCC1: D5.A, J5.72, J5.74
VCC2: D21.A, J11.72, J11.74
VCC3: D31.A, J16.72, J16.74
VCC4: D41.A, J21.72, J21.74
VCC5: D51.A, J26.72, J26.74
VCCIO: C17.1, D16.A, R3.2, R45.1, U1.4, U2.2, U2.8, U2.16
VCCIO1: C41.1, D11.A, R25.1, R34.2, U9.2, U9.8, U9.16, U10.4
VCCIO2: C65.1, D25.A, R61.1, R68.2, U16.2, U16.8, U16.16, U17.4
VCCIO3: C89.1, D35.A, R85.1, R92.2, U22.2, U22.8, U22.16, U23.4
VCCIO4: C113.1, D45.A, R109.1, R116.2, U28.2, U28.8, U28.16, U29.4
VCCIO5: C137.1, D55.A, R133.1, R140.2, U34.2, U34.8, U34.16, U35.4
VIN: C21.+, C23.1, C25.1, D1.C, D2.C, U3.1, U5.8
VIN1: C7.1, C8.1, C10.+, D5.C, D7.C, U7.8, U12.1
VIN2: C50.1, C51.1, C52.+, D21.C, D22.C, U14.8, U18.1
VIN3: C74.1, C75.1, C76.+, D31.C, D32.C, U20.8, U24.1
VIN4: C98.1, C99.1, C100.+, D41.C, D42.C, U26.8, U30.1
VIN5: C122.1, C123.1, C124.+, D51.C, D52.C, U32.8, U36.1
VSIM: C36.2, C38.2, D15.3, J9.C1, U1.41
VSIM1: C26.2, C27.2, D8.3, J8.C1, U10.41
VSIM2: C59.2, C60.2, D23.3, J14.C1, U17.41
VSIM3: C83.2, C84.2, D33.3, J19.C1, U23.41
VSIM4: C107.2, C108.2, D43.3, J24.C1, U29.41
VSIM5: C131.2, C132.2, D53.3, J29.C1, U35.41
V_USB: D1.A, D6.5, F2.2, U1.17
V_USB1: D7.A, D20.5, F1.2, U10.17
V_USB2: D22.A, D30.5, F3.2, U17.17
V_USB3: D32.A, D40.5, F4.2, U23.17
V_USB4: D42.A, D50.5, F5.2, U29.17
V_USB5: D52.A, D60.5, F6.2, U35.17

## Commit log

2023-04-11 Copying in v02 proto design
2023-04-11 datasheets and documentation
2023-04-11 added GNSS antenna U.FL
    -added GNSS antenna U.FL, with supporting circuitry and power control
    -rotated module 90 degrees
2023-04-12 Silk adjustments
2023-04-12 Increase VUSB trace to 30mil
    -u.fl FP library update - adds restrict underneath
2023-04-12 top poly to 7mil and sch cleanup
2023-04-12 USB D+ and D- routing
    -re-did calcs and changed to 9 mil width with 8 mil spacing.
2023-04-12 update LEDs and limiting resistor values to new standards
2023-04-12 added oshw logo
    -also added label to ANT_REG_EN jumper
2023-04-12 library work
    -switching some parts over to SFE libraries
2023-04-14 TVS diodes moved closer to connectors
    -more gnd vias along rf traces and everywhere.
2023-04-14 approving some drc errors
2023-04-17 pre-review changes (part 1)
    -renamed all jumpers to match silk
    -replaced I2C pullups to 2.2K
    -Schematic Cleanup
    -silk lines between tight passives in a row
    -fixed acid trap off of pad 12
    -tweaked via position near GND pad 14 to allow for flow
2023-04-17 Moved VCCIO away from LTE_ANT
2023-04-18 USB_SHLD jumper added
2023-04-18 Sim connector re-routing
    -IC2 ref to U2
    -Updated Nano SIM FP to have tRestrict area underneath
    -moved traces under the SIM connector to bottom layer
2023-04-19 More changes from group review
    -Now it's a 4-layer, removed some 3.3V traces from bottom copper, added vias as necessary to connect to 3.3V inner layer.
    -Changed where regulators (U3 and U5) enable pins are tied up to. They are now tied up to the 3.3V provided by the MM Main board. Previously, they were connected to VIN, which could be higher than 3.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
    -Disconnected V_USB from MM m.2 connector.
2023-04-19 ESD diode position and removed L1
    -Moved ESD diode D10 to the other side of L2, to put it directly next to the u.fl connector
    -removed L1 (it was previously DNP)
2023-04-19 acid traps and measures
    -fixed some acid traps and routed some GNDs off of pads
    -measures to everything
2023-04-20 USB lines updated for correct impedance calcs
    -updated trace width and spacing to hit a 90 ohm differential impedance on D+/D-
    -updated calculation text paragraph in SCH
2023-04-20 ESD diode on D+ and D- USB lines
2023-04-20 RF traces corrected to 12.3mil
    -also updated calc paragraph in SCH
2023-04-21 LED disable jumpers added
    -LTE_RI_LED, LTE_NI_LED, LTE_ON
2023-04-21 add 0.1uF cap on VCCB for level shifter
2023-04-21 Library work and BOM consolidation
2023-04-21 added PTC fuse to USB input
2023-04-24 SIM clock routing to a "Y" to avoid 90 degree.
2023-04-24 Moved LTE "ON" button north away from the M.2 conn
    -note, moved the silk label to the south side of the button to allow this shift.
2023-04-24 SIM clock line re-routed to a "teardrop" instead of 90
2023-04-24 nudging small things
    -nudged via on LTE_18_NI to get better gnd flow
    -EN net nudged to make better gnd flow
    -adjusted measures to avoid overlap with milling text
2023-04-27 LTE_RESET changed to 10K
    -LTE_RESET was not working with 100K, so changed to 10K
    -Moved ANT regulator power control to different F pin, to avoid RX/TX sharing conflict
    -corrected SCH text note about shared pins for RX1/TX1 on esp32
    -corrected RTS1/CTS1 back so they are not swapped on this FB.
2023-05-01 Eng run checklist
    -Minor schematic cleanup and tightening
    -added some jumper text objects to sch
    -added layer 1/2/3/4 text to copper layers
    -switched to larger TP
    -bumper version to v10
2023-05-01 production panel v10
    -Note, I also added some more specific ordering instructions to the single brd file, that were flagged by the panelizer tool. No changed to the design though.
2023-05-01 minor sch aesthetic updates
    -changed one V_USB flag to a power symbol
    -updated version in s SCH to v10
2023-05-01 added version number into the gerber zip file name
2023-05-22 Corrected RTS pulldown - bumped to v11
    -Pull down was incorrectly on CTS. It is now correctly on RTS.
    -DIR of channels 3/4 on U2 have also been corrected to reflect RTS/CTS as needed.
    -bumped version to v11
2023-05-31 R33 set to DNP (EN pullup on vreg)
    -R33 is DNP. This was conflicting with GPIO12 (strapping pin) on the ESP32 PB
    -R46 changed to 100 for brighter green LED.
2023-05-31 Update Documents Folder for SARA-R510M8S-01B
2023-05-31 v11 production panel and gerbers
2023-07-12 On LED changed to Red (DIO-17976)
2023-08-10 Push Docs to Main Branch
2023-08-10 Remove copy site folder since this will be deployed in gh-pages branch
2023-08-10 Force push
2023-08-10 Remove copy of site since this is in gh-pages branch
2023-08-12 Update introduction.md
    fix broken link (copy pasta error...)
2023-11-14 Remove "Hide" from Style
    - Remove the "hide" from the style to ensure that the images/tutorials show up when printing
2023-11-14 Deployed e9c708c with MkDocs version: 1.5.3
2024-10-28 Add cookies
2024-10-29 Deployed c6ccd8d with MkDocs version: 1.6.1
2026-06-03 Deployed 03c1400 with MkDocs version: 1.6.1
